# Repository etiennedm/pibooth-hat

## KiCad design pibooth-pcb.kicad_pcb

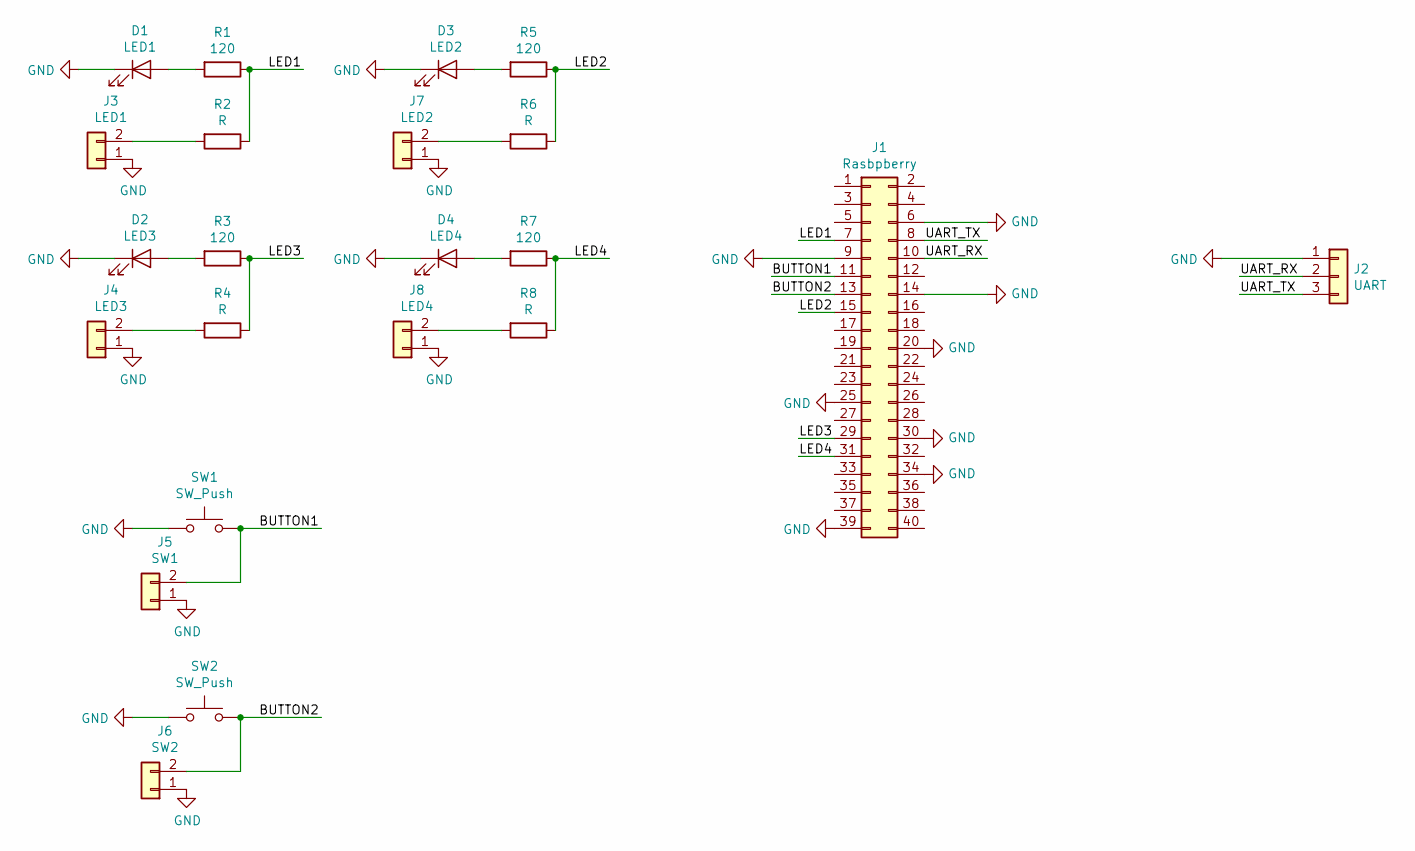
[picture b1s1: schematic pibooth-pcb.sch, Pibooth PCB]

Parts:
D1: LED1; LED_D3.0mm_Horizontal_O1.27mm_Z2.0mm_Clear
D2: LED3; LED_D3.0mm_Horizontal_O1.27mm_Z2.0mm_Clear
D3: LED2; LED_D3.0mm_Horizontal_O1.27mm_Z2.0mm_Clear
D4: LED4; LED_D3.0mm_Horizontal_O1.27mm_Z2.0mm_Clear
J1: Rasbpberry; PinHeader_2x20_P2.54mm_Vertical
J2: UART; PinHeader_1x03_P2.54mm_Vertical
J3: LED1; Molex_KK-254_AE-6410-02A_1x02_P2.54mm_Vertical
J4: LED3; Molex_KK-254_AE-6410-02A_1x02_P2.54mm_Vertical
J5: SW1; Molex_KK-254_AE-6410-02A_1x02_P2.54mm_Vertical
J6: SW2; Molex_KK-254_AE-6410-02A_1x02_P2.54mm_Vertical
J7: LED2; Molex_KK-254_AE-6410-02A_1x02_P2.54mm_Vertical
J8: LED4; Molex_KK-254_AE-6410-02A_1x02_P2.54mm_Vertical
R1, R3, R5, R7: 120; R_Axial_DIN0207_L6.3mm_D2.5mm_P10.16mm_Horizontal
R2, R4, R6, R8: R; R_Axial_DIN0207_L6.3mm_D2.5mm_P10.16mm_Horizontal
SW1, SW2: SW_Push; SW_SPST_TL3342

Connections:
/BUTTON1: J1.11, J5.2, SW1.2
/BUTTON2: J1.13, J6.2, SW2.2
/LED1: J1.7, R1.1, R2.1
/LED2: J1.15, R5.1, R6.1
/LED3: J1.29, R3.1, R4.1
/LED4: J1.31, R7.1, R8.1
/UART_RX: J1.10, J2.2
/UART_TX: J1.8, J2.3
GND: D1.1 (K), D2.1 (K), D3.1 (K), D4.1 (K), J1.6, J1.9, J1.14, J1.20, J1.25, J1.30, J1.34, J1.39, J2.1, J3.1, J4.1, J5.1, J6.1, J7.1, J8.1, SW1.1, SW2.1
unnamed: D1.2 (A), R1.2
unnamed: D2.2 (A), R3.2
unnamed: D3.2 (A), R5.2
unnamed: D4.2 (A), R7.2
unnamed: J3.2, R2.2
unnamed: J4.2, R4.2
unnamed: J7.2, R6.2
unnamed: J8.2, R8.2

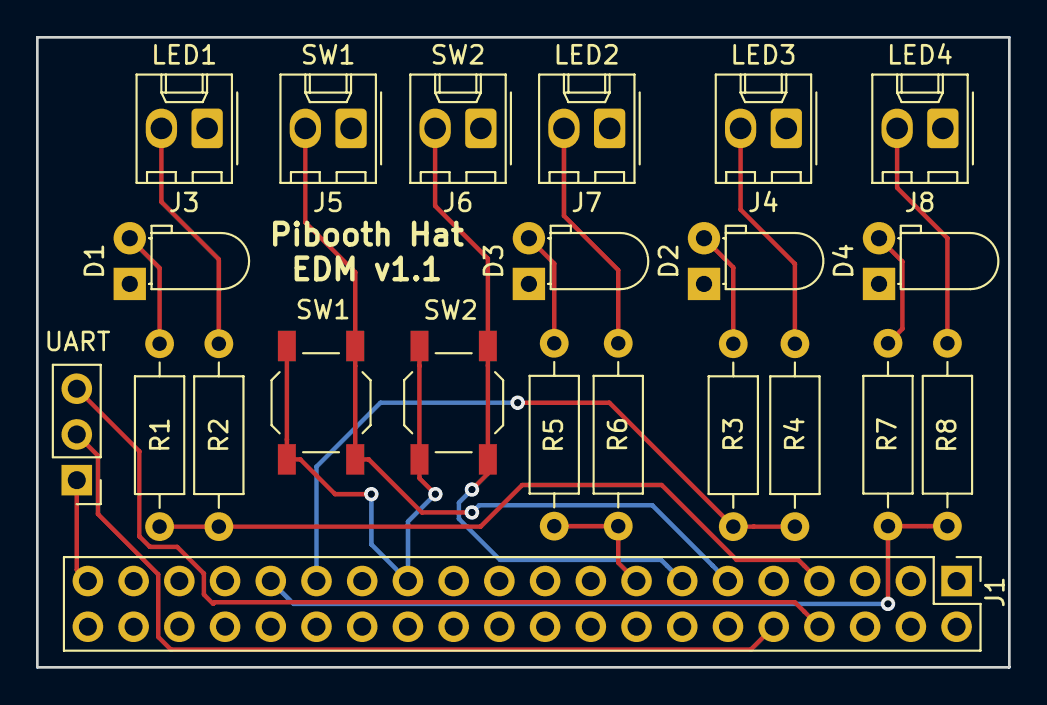
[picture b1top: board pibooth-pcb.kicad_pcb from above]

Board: 2 copper layers, 54.0 x 35.0 mm, 22 parts (0 on the bottom side), 17 nets.

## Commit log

2019-02-26 Initial commit of Pibooth hat EDA project
2019-04-24 Fix wrong pi header orientation
